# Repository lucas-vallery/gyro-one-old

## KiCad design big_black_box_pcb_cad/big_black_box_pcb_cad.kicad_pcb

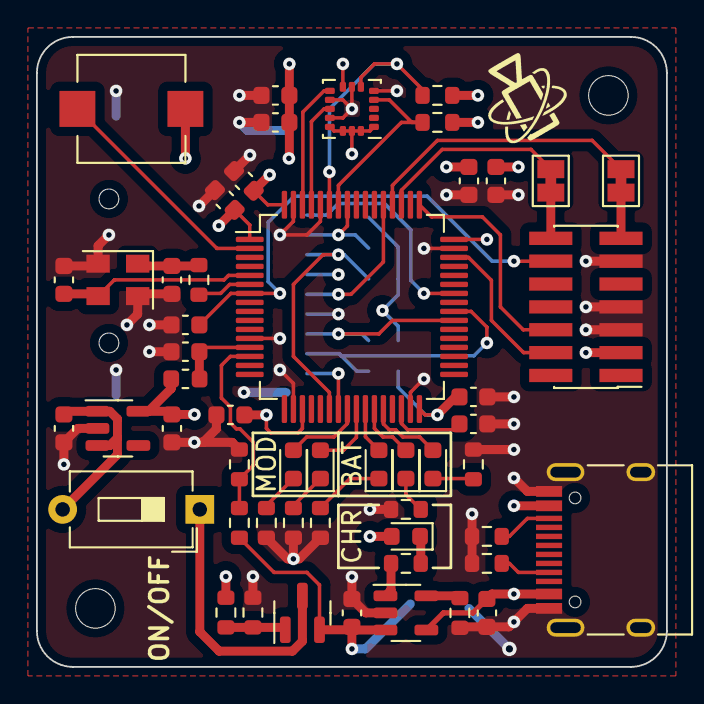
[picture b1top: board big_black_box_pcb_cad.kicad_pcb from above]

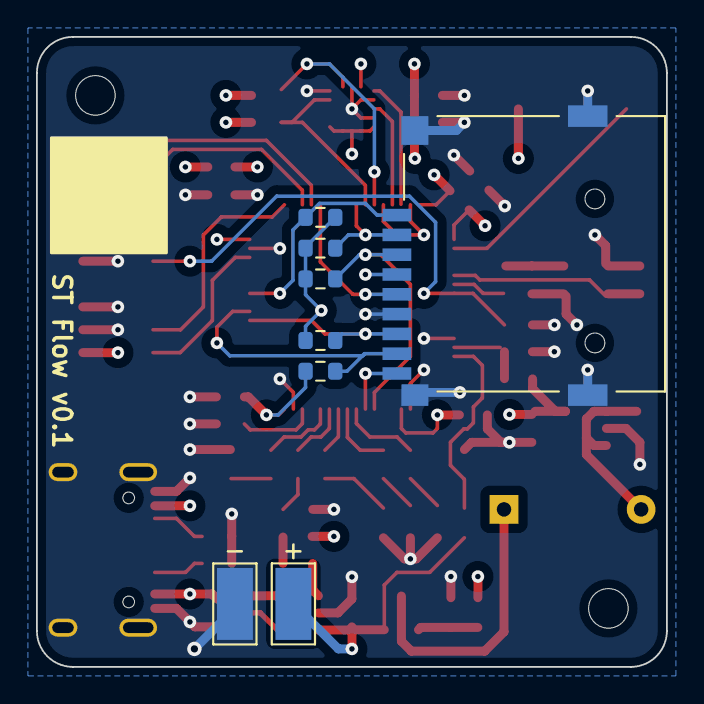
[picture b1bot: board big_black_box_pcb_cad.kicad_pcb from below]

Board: 4 copper layers, 35.0 x 35.0 mm, 62 parts (8 on the bottom side), 47 nets.

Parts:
C101: 10uF; C_0603_1608Metric
C102, C104, C107, C108, C109, C110, C112: 100nF; C_0603_1608Metric
C103, C111, C116, C117: 4.7uF; C_0603_1608Metric
C105, C106: 12pF; C_0603_1608Metric
C113, C114, C115: 1uF; C_0603_1608Metric
D101, D102, D103, D104, D105, D106: LED; LED_0603_1608Metric
FB101: 600R@100MHz; L_0603_1608Metric
H101, H102: MountingHole_Pad; MountingHole_2.2mm_M2_ISO14580
J101: USB_C_Receptacle_USB2.0; USB_C_Receptacle_HRO_TYPE-C-31-M-12
J102: Conn_02x07_Odd_Even; PinHeader_2x07_P1.27mm_Vertical_SMD
JP101, JP102: SolderJumper_2_Bridged; SolderJumper-2_P1.3mm_Bridged_Pad1.0x1.5mm
Q101: TP0610T; SOT-23
R101, R102: 5.1k; R_0603_1608Metric
R103, R104, R106, R114, R115: 10k; R_0603_1608Metric
R105: 1.2k; R_0603_1608Metric
R107: 12k; R_0603_1608Metric
R108, R109, R110, R111, R112, R113: 470; R_0603_1608Metric
R116: ??; R_0603_1608Metric
R117, R118, R120, R121, R122: 47k; R_0603_1608Metric
SW101: SW_Push; SW_SPST_B3U-1000P
SW102: SW_DIP_x01; SW_DIP_SPSTx01_Slide_6.7x4.1mm_W7.62mm_P2.54mm_LowProfile
TP101, TP102: TestPoint; TestPoint_Pad_2.0x2.0mm
U101: STM32F412RGTx; LQFP-64_10x10mm_P0.5mm
U102: ST_LIS3DHTR; LGA-16_3x3mm_P0.5mm_LayoutBorder3x5y
U103: MCP1802x-xx02xOT; SOT-23-5
U104: MCP73831-2-OT; SOT-23-5
U105: sd_slot_lcsc; sd_lcsc
Y101: 16 Mhz; Crystal_SMD_EuroQuartz_MT-4Pin_3.2x2.5mm

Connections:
+5V: C116.1, D101.2 (A), J101.A4 (VBUS), J101.A9 (VBUS), J101.B4 (VBUS), J101.B9 (VBUS), R116.1, U104.4 (VDD)
/CC1: J101.A5 (CC1), R101.1
/CC2: J101.B5 (CC2), R102.1
BAT_SENSE: R114.2, R115.1, U101.14 (PA0)
CEL+: C117.1, Q101.2 (S), R114.1, TP102.1, U104.3 (VBAT)
GND: C101.2, C102.2, C103.1, C104.2, C105.2, C106.2, C107.2, C108.2, C109.2, C110.2, C111.2, C112.2, C113.2, C114.2, C115.2, C116.2, C117.2, J101.A1 (GND), J101.A12 (GND), J101.B1 (GND), J101.B12 (GND), J101.S1 (SHIELD), J102.5, J102.7, J102.11, R101.2, R102.2, R106.2, R107.2, R109.2, R110.2, R111.2, R112.2, R113.2, R115.2, TP101.1, U101.12 (VSSA), U101.18 (VSS), U101.31 (VSS), U101.47 (VSS), U101.60 (BOOT0), U101.63 (VSS), U102.5 (GND), U102.7 (SDO/SA0), U102.10 (RES), U102.12 (GND), U103.2 (GND), U104.2 (VSS), U105.6 (VSS), U105.10 (EH), U105.11 (EH), U105.12 (EH), U105.13 (EH), Y101.2, Y101.4
GYRO_IRQ1: U101.61 (PB8), U102.11 (INT1)
GYRO_IRQ2: U101.62 (PB9), U102.9 (INT2)
GYRO_SCL: R104.2, U101.58 (PB6), U102.4 (SCL_SPC)
GYRO_SDA: R103.2, U101.59 (PB7), U102.6 (SDA/SDI/SDO)
JTAG_NRST: C104.1, J102.12, U101.7 (NRST)
JTAG_SWCLK: J102.6, U101.49 (PA14)
JTAG_SWDIO: J102.4, U101.46 (PA13)
JTAG_UART_RX: JP101.1 (A), U101.52 (PC11)
JTAG_UART_TX: JP102.2 (B), U101.51 (PC10)
LED_1: D102.2 (A), U101.24 (PC4)
LED_2: D103.2 (A), U101.25 (PC5)
LED_3: D104.2 (A), U101.26 (PB0)
LED_4: D105.2 (A), U101.27 (PB1)
LED_5: D106.2 (A), U101.28 (PB2)
MCU_VBAT: C101.1, C102.1, C107.1, C108.1, C109.1, C110.1, C111.1, C113.1, C115.1, FB101.1, J102.3, R103.1, R104.1, R117.1, R118.1, R120.1, R121.1, R122.1, SW101.2, U101.1 (VBAT), U101.19 (VDD), U101.32 (VDD), U101.48 (VDD), U101.64 (VDD), U102.1 (VDD_IO), U102.8 (CS), U102.13 (ADC3), U102.14 (VDD), U102.15 (ADC2), U102.16 (ADC1), U103.5 (VOUT), U105.4 (VDD)
MCU_VREF+: C112.1, FB101.2, U101.13 (VDDA)
unnamed: C103.2, U101.30 (VCAP_1)
unnamed: C105.1, U101.5 (PH0), Y101.3
unnamed: C106.1, R105.2, Y101.1
unnamed: D101.1 (K), R108.2
unnamed: D102.1 (K), R109.1
unnamed: D103.1 (K), R110.1
unnamed: D104.1 (K), R111.1
unnamed: D105.1 (K), R112.1
unnamed: D106.1 (K), R113.1
unnamed: J102.13, JP101.2 (B)
unnamed: J102.14, JP102.1 (A)
unnamed: Q101.1 (G), R106.1, R116.2
unnamed: Q101.3 (D), SW102.1
unnamed: R105.1, U101.6 (PH1)
unnamed: R107.1, U104.5 (PROG)
unnamed: R108.1, U104.1 (STAT)
SD_CD: U101.23 (PA7), U105.9 (CD)
SD_CLK: U101.53 (PC12), U105.5 (CLK)
SD_CMD: R120.2, U101.22 (PA6), U105.3 (CMD)
SD_D0: R118.2, U101.39 (PC8), U105.7 (DAT0)
SD_D1: R117.2, U101.40 (PC9), U105.8 (DAT1)
SD_D2: R122.2, U101.42 (PA9), U105.1 (DAT2)
SD_D3: R121.2, U101.57 (PB5), U105.2 (CD/DAT3)
USER_BTN_IRQ: SW101.1, U101.2 (PC13)
VBAT: C114.1, SW102.2, U103.1 (VIN), U103.3 (~SHDN)

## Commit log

2024-06-05 Add kicad files
